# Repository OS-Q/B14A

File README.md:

# [B14A](https://github.com/OS-Q/B14A)

[B14A](https://github.com/OS-Q/B14A) 标准硬件模组应用 [P14](https://github.com/OS-Q/P14) 进行开发

### [Q = (OpenSource & OperatingSystem) ](http://www.OS-Q.com)

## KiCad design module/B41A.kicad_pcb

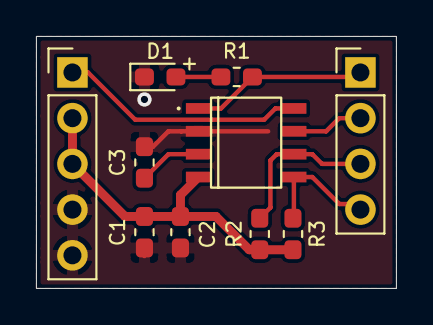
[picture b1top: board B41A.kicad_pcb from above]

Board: 2 copper layers, 20.0 x 14.0 mm, 10 parts (0 on the bottom side), 9 nets.

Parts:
C1, C3: 1uF; C_0603_1608Metric_Pad1.05x0.95mm_HandSolder
C2: 100nF; C_0603_1608Metric_Pad1.05x0.95mm_HandSolder
D1: LED; LED_0603_1608Metric_Pad1.05x0.95mm_HandSolder
J1: Conn_01x05_Male; PinHeader_1x05_P2.54mm_Vertical
J2: Conn_01x04_Male; PinHeader_1x04_P2.54mm_Vertical
R1: 2K; R_0603_1608Metric_Pad1.05x0.95mm_HandSolder
R2, R3: 4.7K; R_0603_1608Metric_Pad1.05x0.95mm_HandSolder
U1: STM8S001J3M; SO8N

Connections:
/SWIM: J1.1, U1.8
/VCAP: C3.1, U1.3
/VDD: C1.1, C2.1, J1.2, J1.3, R2.1, R3.2, U1.4
GND: C1.2, C2.2, C3.2, D1.1, J1.4, J1.5, U1.2
unnamed: D1.2, R1.2
unnamed: J2.1, R1.1, U1.1
unnamed: J2.2, U1.7
unnamed: J2.3, R2.2, U1.6
unnamed: J2.4, R3.1, U1.5

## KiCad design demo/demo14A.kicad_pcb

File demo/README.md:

# STM8S001 Break-Out Board with RS485 and DS1621S Thermometer

### 工程源自 https://github.com/TG9541/stm8s001rs485

---

This KiCad project provides a small PCB with an STM8S001J3M3, a RS485 interface and a DS1621S temperature sensor. Applications include [MODBUS with STM8 eForth](https://github.com/TG9541/stm8ef-modbus).

The STM8S001J3M3 is a member of the "STM8S Low Density" family that's based on the "STM8S Access Line" cross-breed STM8S903, which, compared with the STM8S003, has some ([undocumented](https://github.com/TG9541/stm8ef/wiki/STM8-Low-Density-Devices#stm8s001j3)) goodies.

The board is supported by [STM8 eForth](https://github.com/TG9541/stm8ef/) which means that it runs an interactive development system on the chip: the serial interface for the console can either use RS485, or a two-wire interface on the GPIO PC5.

A µC with merrily 5 GPIO pins is a good shield against feature creep, but the following things "had" to be included:

* most GPIOs, including the I2C bus (PB4 & PB5), and an analog input or timer output (PC5) and the are available on 6 pin header
* a narrow PCB for a cylindrical sensors with a diameter of 7mm
* 5V nominal supply, internal 3.3V power supply with an LDO regulator
* signalling LEDs for RS485 activity (RxTx) and direction (Tx)

Care should be taken not to exceed 6V input supply voltage. The internal 3.3V power supply is available on the header pin J2.1 (it should be able to support about 150mA).

## Design

The design is simple: The STM8S001J3 controls the direction of the SP3485 with PA1/PD6. R3 makes sure that the SWIM interface is still usable when the SP3485 is in "/RE" mode (i.e. listening for RS485 communication).

The RS485 communcation direction is "send" when LED D1 is active. Communication is indecated by pulses on LED D2. Bright pulsing means read, and dim pulses means write. R4 is the (optional) RS485 termination resistor.

The BOM is in the docs folder.

## Pin Headers

Pin headers are also optional: they allow the board to be used as a module for quickly building a MODBUS node with a "perfboard" (using I2C or GPIOs), but connecting wires directly is also an intended use case.

### Description Header J1
Pin|Signal
-|-
1|3.4 to 6V for XC6206 3.3V LDO regulator
2|GND
3|RS485 "A" (optional 120R termination)
4|RS485 "B"

### Description Header J2
Pin|Tag|Pin STM8S001|GPIO|Features
-|-|-|-|-
1|3.3|4|VDD|3.3V from LDO regulator
2||8|PC6 | SPI_MOSI, [TIM1_CH1]
2|SWIM|8|PD1 | **SWIM**
2||8|PD3 | TIM2_CH2, TIM2_CH2, ADC_ETR
2||8|PD5 | **UART1_TX**, AIN5
3||5|PA3 | TIM2_CH3, [SPI_NSS], [UART1_TX]
3|SDA|5|PB5 | **I2C_SDA**
4||7|PC3 | TIM1_CH3, [TLI], [TIM1_CH1N]
4||7|PC4 | TIM1_CH4, CLK_CCO, AIN2, [TIM1_CH3]
4|PC5|7|PC5 | SPI_SCK, [TIM2_CH1]
5|SCL|6|PB4 | **I2C_SCL**, [ADC_ETR]
6|GND|2|VSS|GND

## PCB and Assembly

Components occupy both sides of a PCB of 33.4mm x 1/4" (the minimal width supported by Oshpark).

On the front side there is the STM8S001J3M3, a XC6206 3.3V LDO regulator, some passive components, and the RS485 signalling LEDs:

A generic 3.3V RS485 transceiver (like SP3485 or MAX3485l) and the (optional) DS1621S thermometer chip are on the backside:

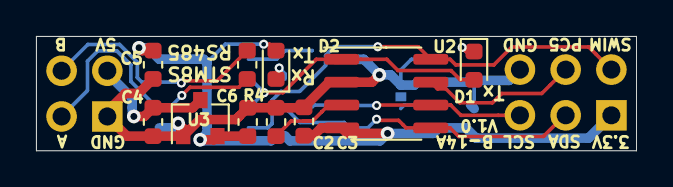
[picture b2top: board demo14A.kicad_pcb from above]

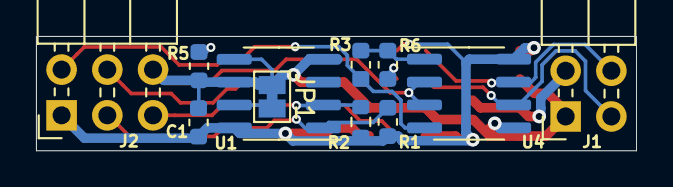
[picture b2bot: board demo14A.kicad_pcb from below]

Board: 2 copper layers, 33.3 x 6.3 mm, 21 parts (11 on the bottom side), 15 nets.

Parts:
C1, C3, C5: 100nF; C_0603_1608Metric
C2, C4, C6: 1uF; C_0603_1608Metric
D1: LED red; LED_0603_1608Metric
D2: LED green; LED_0603_1608Metric
J1: Conn_02x02_Odd_Even; PinHeader_2x02_P2.54mm_Horizontal
J2: Conn_02x03_Counter_Clockwise; PinHeader_2x03_P2.54mm_Horizontal
JP1: A0; SolderJumper-2_P1.3mm_Bridged_Pad1.0x1.5mm
R1, R2, R3, R5, R6: 4k7; R_0603_1608Metric
R4: 120R; R_0603_1608Metric
U1: DS1621S; SOIC-8_3.9x4.9mm_P1.27mm
U2: STM8S001J3M; SOIC-8_3.9x4.9mm_P1.27mm
U3: XC6206P332MR; SOT-23
U4: SP3485CN; SOIC-8_3.9x4.9mm_P1.27mm

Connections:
+3V3: C1.2, C3.2, C5.2, C6.2, D2.2, J2.1, R1.1, R2.1, U1.8, U2.4, U3.2, U4.8
+5V: C4.2, J1.2, U3.3
/A: J1.3, R4.1, U4.6
/B: J1.4, R4.2, U4.7
/DIR.RX: D1.2, U2.1, U4.2, U4.3
/PC5: J2.4, U2.7
/SCL: J2.5, R2.2, U1.2, U2.6
/SDA: J2.3, R1.2, U1.1, U2.5
/SWIM.TX: J2.2, R3.1, U2.8, U4.4
GND: C1.1, C2.1, C3.1, C4.1, C5.1, C6.1, J1.1, J2.6, JP1.1, R5.2, U1.4, U1.5, U1.6, U2.2, U3.1, U4.5
unnamed: C2.2, U2.3
unnamed: D1.1, R5.1
unnamed: D2.1, R6.1
unnamed: JP1.2, U1.7
unnamed: R3.2, R6.2, U4.1

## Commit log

2021-03-03 init
